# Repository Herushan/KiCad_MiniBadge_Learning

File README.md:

# KiCad_MiniBadge_Learning
The files used for the KiCad MiniBadge Learning YouTube series. 
YouTube to first video [Episode One or Step One of making your own minibadge](https://youtu.be/156MaRJBwHk?si=-d4g35n8yYzdG-6n).
Currently files up to video 2.

Using KiCad 8 I go through the steps of making a minibadge and some of the settings and atributes to go with it. This is the KiCad documents and files for the project that I created and run through in the videos.

Files are updated to KiCad 9 with some minor changes to the PCB (added text and flipped the through hole LED)

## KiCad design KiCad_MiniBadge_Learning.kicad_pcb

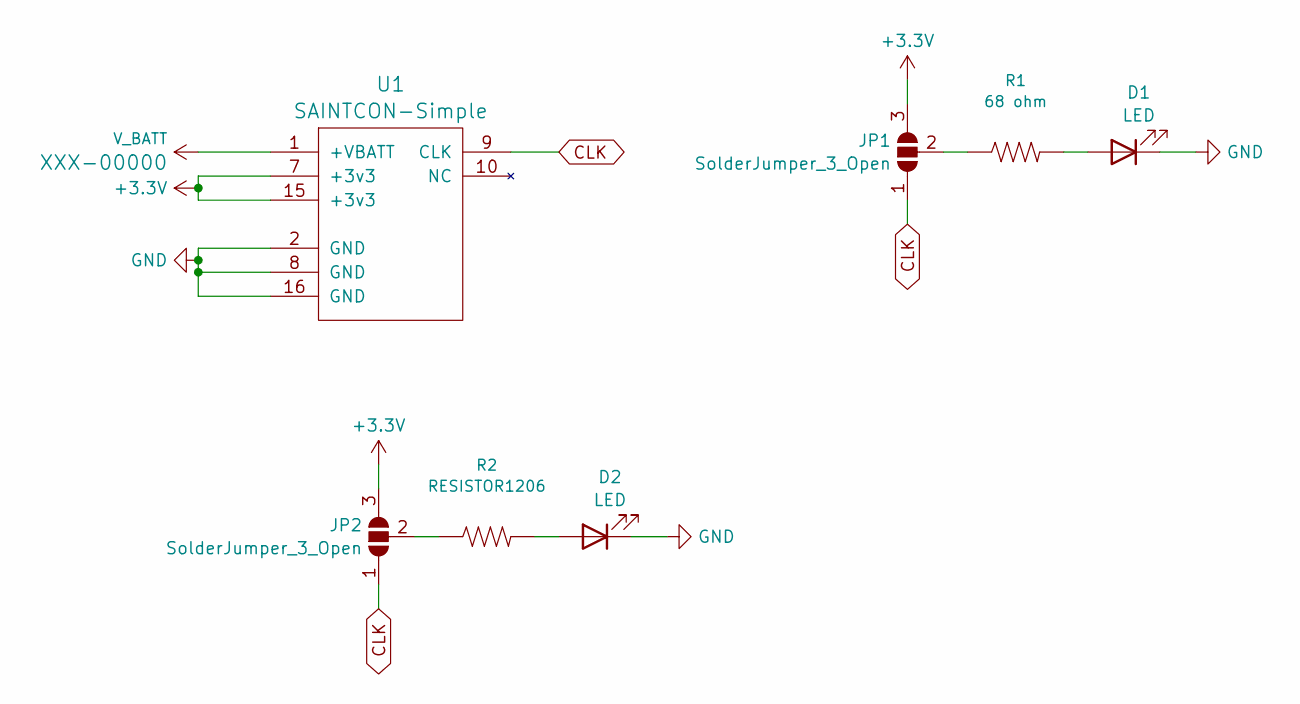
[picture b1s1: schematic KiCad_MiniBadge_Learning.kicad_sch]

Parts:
D1: LED; LED_1206_3216Metric_Pad1.42x1.75mm_HandSolder
D2: LED; LED_D3.0mm
JP1, JP2: SolderJumper_3_Open; SolderJumper-3_P1.3mm_Open_RoundedPad1.0x1.5mm
R1: 68 ohm; R_1206_HandSoldering
R2: RESISTOR1206; R_1206_HandSoldering
U1: SAINTCON-Simple; SAINTCON-Minibadge-minimal

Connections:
+3.3V: JP1.3 (B), JP2.3 (B), U1.7 (+3v3), U1.15 (+3v3)
CLK: JP1.1 (A), JP2.1 (A), U1.9 (CLK)
GND: D1.1 (K), D2.1 (K), U1.2 (GND), U1.8 (GND), U1.16 (GND)
unnamed: D1.2 (A), R1.2
unnamed: D2.2 (A), R2.2
unnamed: JP1.2 (C), R1.1
unnamed: JP2.2 (C), R2.1
V_BATT: U1.1 (+VBATT)

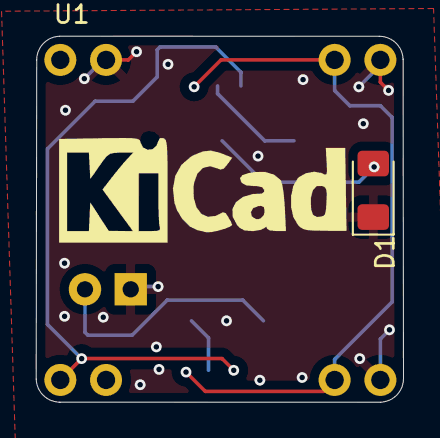
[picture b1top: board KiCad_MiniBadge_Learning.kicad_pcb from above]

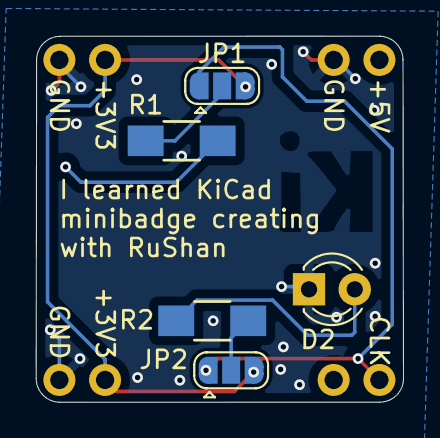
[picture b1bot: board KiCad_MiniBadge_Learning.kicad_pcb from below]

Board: 2 copper layers, 20.4 x 20.3 mm, 7 parts (5 on the bottom side), 7 nets.

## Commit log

2024-09-22 Create Gerbers
2024-09-22 Create Test
